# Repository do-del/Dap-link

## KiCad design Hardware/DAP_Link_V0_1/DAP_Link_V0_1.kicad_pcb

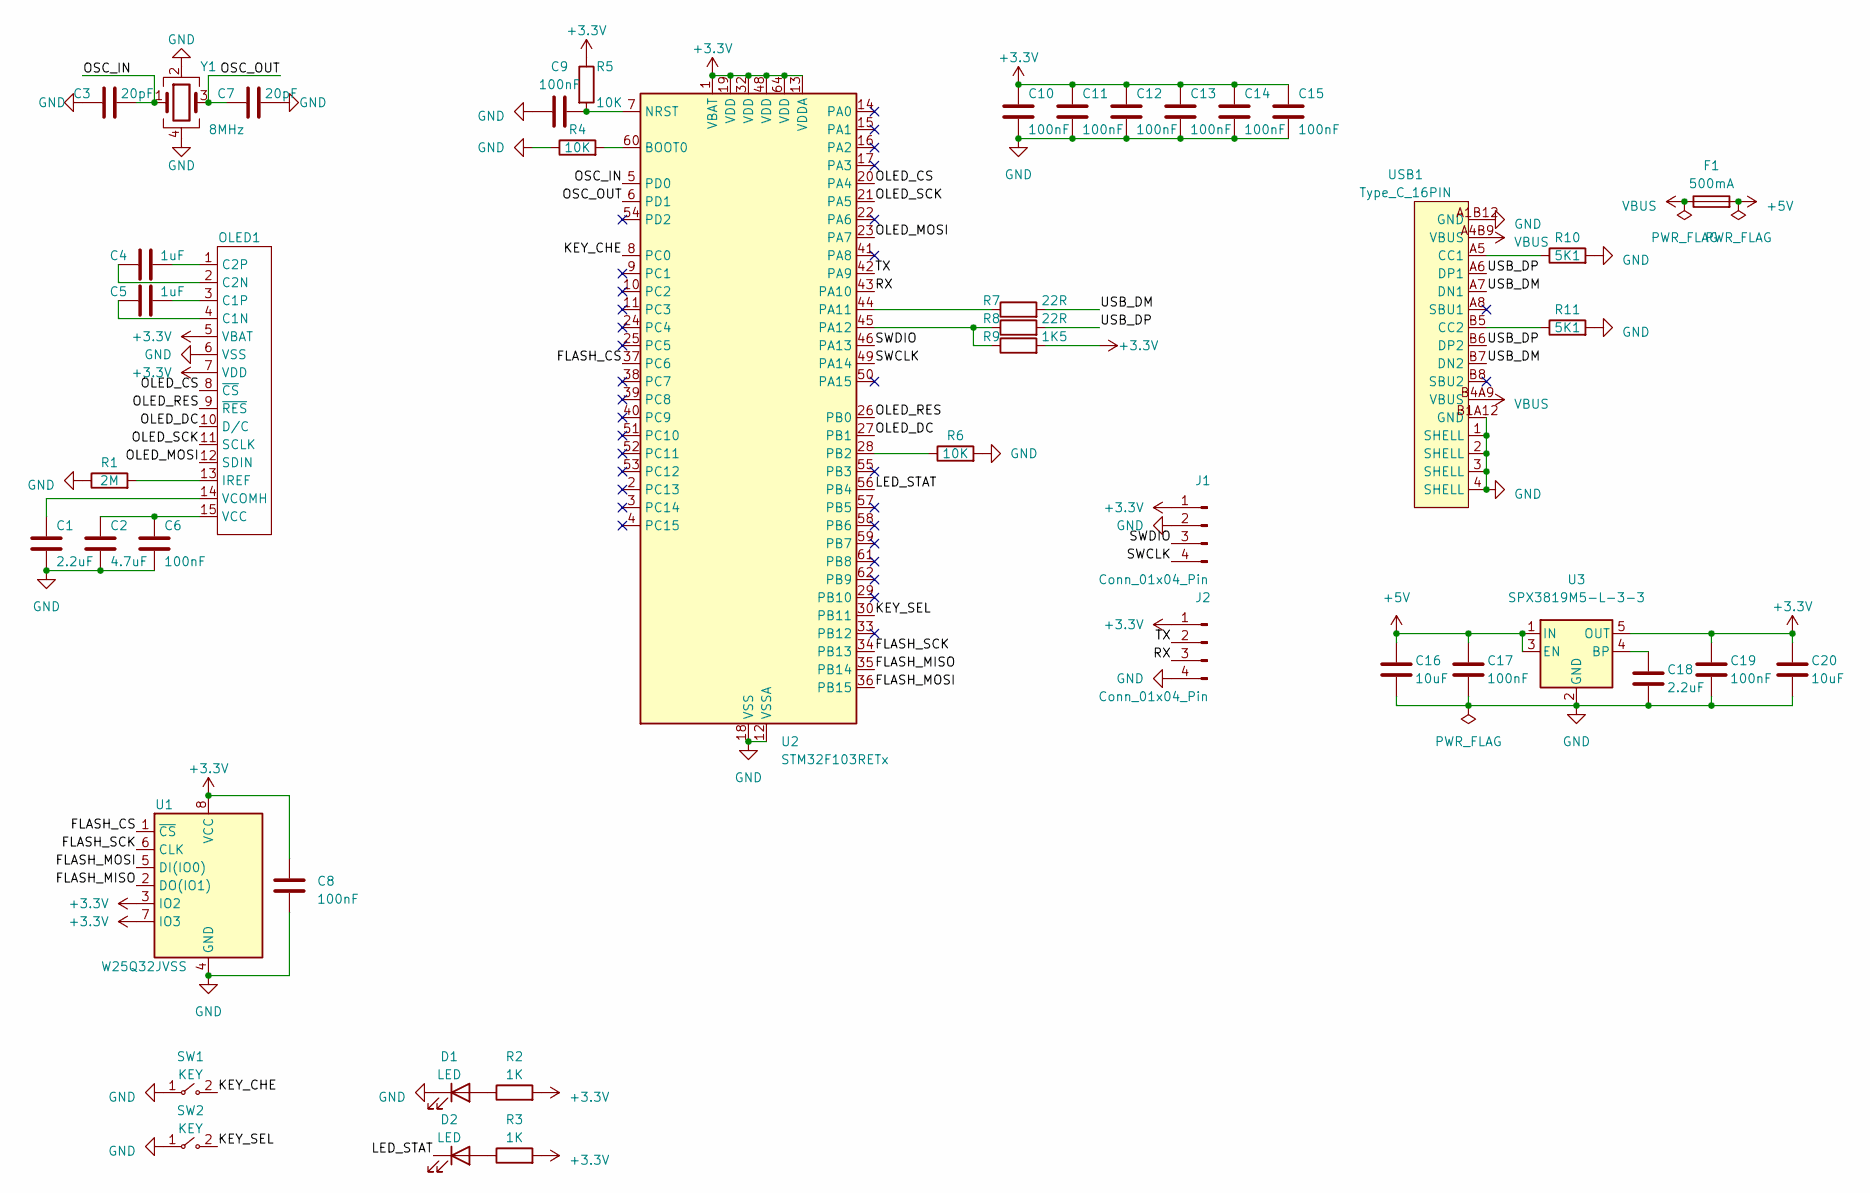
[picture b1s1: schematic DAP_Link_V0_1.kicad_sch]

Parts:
C1, C18: 2.2uF; C_0603_1608Metric_Pad1.08x0.95mm_HandSolder
C2: 4.7uF; C_0603_1608Metric_Pad1.08x0.95mm_HandSolder
C3, C7: 20pF; C_0603_1608Metric_Pad1.08x0.95mm_HandSolder
C4, C5: 1uF; C_0603_1608Metric_Pad1.08x0.95mm_HandSolder
C6, C8, C9, C10, C11, C12, C13, C14, C15, C17, C19: 100nF; C_0603_1608Metric_Pad1.08x0.95mm_HandSolder
C16, C20: 10uF; C_0603_1608Metric_Pad1.08x0.95mm_HandSolder
D1, D2: LED; LED_0603_1608Metric_Pad1.05x0.95mm_HandSolder
F1: 500mA; Fuse_1206_3216Metric
J1: Conn_01x04_Pin; SH1.0mm_4P_WT
J2: Conn_01x04_Pin; Conn_2.54_01x04_SMD_V
OLED1: 0.91_OLED_15P
R1: 2M; R_0603_1608Metric_Pad0.98x0.95mm_HandSolder
R2, R3: 1K; R_0603_1608Metric_Pad0.98x0.95mm_HandSolder
R4, R5, R6: 10K; R_0603_1608Metric_Pad0.98x0.95mm_HandSolder
R7, R8: 22R; R_0603_1608Metric_Pad0.98x0.95mm_HandSolder
R9: 1K5; R_0603_1608Metric_Pad0.98x0.95mm_HandSolder
R10, R11: 5K1; R_0603_1608Metric_Pad0.98x0.95mm_HandSolder
SW1, SW2: KEY; SW_3x4
U1: W25Q32JVSS; SOIC-8_5.23x5.23mm_P1.27mm
U2: STM32F103RETx; LQFP-64_10x10mm_P0.5mm
U3: SPX3819M5-L-3-3; SOT-23-5
USB1: Type_C_16PIN; TYPE-C-16PIN_SMD
Y1: 8MHz; Crystal_SMD_3225-4Pin_3.2x2.5mm

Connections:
+3.3V: C8.2, C10.1, C11.1, C12.1, C13.1, C14.1, C15.1, C19.1, C20.1, J1.1, J2.1, OLED1.5 (VBAT), OLED1.7 (VDD), R2.2, R3.2, R5.1, R9.2, U1.3 (IO2), U1.7 (IO3), U1.8 (VCC), U2.1 (VBAT), U2.13 (VDDA), U2.19 (VDD), U2.32 (VDD), U2.48 (VDD), U2.64 (VDD), U3.5 (OUT)
+5V: C16.1, C17.1, F1.2, U3.1 (IN), U3.3 (EN)
/FLASH_CS: U1.1 (~CS), U2.37 (PC6)
/FLASH_MISO: U1.2 (DO(IO1)), U2.35 (PB14)
/FLASH_MOSI: U1.5 (DI(IO0)), U2.36 (PB15)
/FLASH_SCK: U1.6 (CLK), U2.34 (PB13)
/KEY_CHE: SW1.2 (B), U2.8 (PC0)
/KEY_SEL: SW2.2 (B), U2.30 (PB11)
/LED_STAT: D2.1 (K), U2.56 (PB4)
/OLED_CS: OLED1.8 (~CS), U2.20 (PA4)
/OLED_DC: OLED1.10 (D/C), U2.27 (PB1)
/OLED_MOSI: OLED1.12 (SDIN), U2.23 (PA7)
/OLED_RES: OLED1.9 (~RES), U2.26 (PB0)
/OLED_SCK: OLED1.11 (SCLK), U2.21 (PA5)
/OSC_IN: C3.2, U2.5 (PD0), Y1.1
/OSC_OUT: C7.1, U2.6 (PD1), Y1.3
/RX: J2.3, U2.43 (PA10)
/SWCLK: J1.4, U2.49 (PA14)
/SWDIO: J1.3, U2.46 (PA13)
/TX: J2.2, U2.42 (PA9)
/USB_DM: R7.2, USB1.A7 (DN1), USB1.B7 (DN2)
/USB_DP: R8.2, USB1.A6 (DP1), USB1.B6 (DP2)
GND: C1.2, C2.2, C3.1, C6.2, C7.2, C8.1, C9.1, C10.2, C11.2, C12.2, C13.2, C14.2, C15.2, C16.2, C17.2, C18.2, C19.2, C20.2, D1.1 (K), J1.2, J2.4, OLED1.6 (VSS), R1.1, R4.1, R6.2, R10.2, R11.2, SW1.1 (A), SW2.1 (A), U1.4 (GND), U2.12 (VSSA), U2.18 (VSS), U2.31 (VSS), U2.47 (VSS), U2.63 (VSS), U3.2 (GND), USB1.1 (SHELL), USB1.2 (SHELL), USB1.3 (SHELL), USB1.4 (SHELL), USB1.A1B12 (GND), USB1.B1A12 (GND), Y1.2, Y1.4
unnamed: D1.2 (A), R2.1
unnamed: D2.2 (A), R3.1
unnamed: C5.1, OLED1.4 (C1N)
unnamed: C5.2, OLED1.3 (C1P)
unnamed: C4.1, OLED1.2 (C2N)
unnamed: C4.2, OLED1.1 (C2P)
unnamed: OLED1.13 (IREF), R1.2
unnamed: C2.1, C6.1, OLED1.15 (VCC)
unnamed: C1.1, OLED1.14 (VCOMH)
unnamed: R4.2, U2.60 (BOOT0)
unnamed: C9.2, R5.2, U2.7 (NRST)
unnamed: R7.1, U2.44 (PA11)
unnamed: R8.1, R9.1, U2.45 (PA12)
unnamed: R6.1, U2.28 (PB2)
unnamed: C18.1, U3.4 (BP)
unnamed: R10.1, USB1.A5 (CC1)
unnamed: R11.1, USB1.B5 (CC2)
VBUS: F1.1, USB1.A4B9 (VBUS), USB1.B4A9 (VBUS)

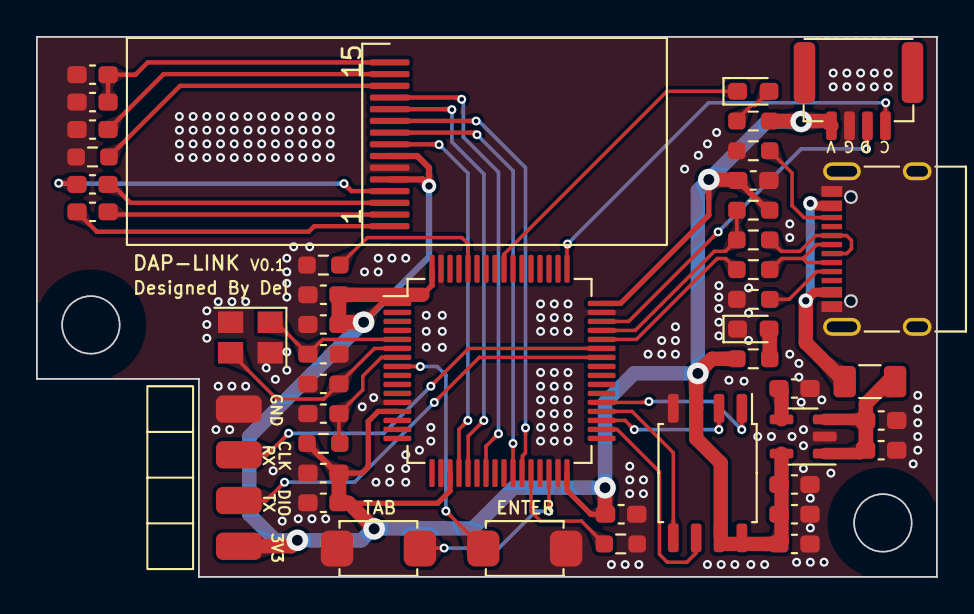
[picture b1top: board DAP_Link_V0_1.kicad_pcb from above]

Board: 2 copper layers, 50.0 x 30.0 mm, 44 parts (0 on the bottom side), 41 nets.

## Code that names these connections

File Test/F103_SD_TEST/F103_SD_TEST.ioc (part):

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Mcu.Name=STM32F103C(8-B)Tx
Mcu.Package=LQFP48
Mcu.UserName=STM32F103C8Tx
PA11.Mode=Device
PA11.Signal=USB_DM
PA12.Mode=Device
PA12.Signal=USB_DP
PA13.Mode=Serial_Wire
PA13.Signal=SYS_JTMS-SWDIO
PA14.Mode=Serial_Wire
PA14.Signal=SYS_JTCK-SWCLK
PA4.GPIOParameters=GPIO_Speed
PA4.GPIO_Speed=GPIO_SPEED_FREQ_HIGH
PA4.Signal=GPIO_Output
PA5.Mode=Full_Duplex_Master
PA5.Signal=SPI1_SCK
PA6.Mode=Full_Duplex_Master
PA6.Signal=SPI1_MISO
PA7.Mode=Full_Duplex_Master
PA7.Signal=SPI1_MOSI
PC14-OSC32_IN.Mode=LSE-External-Oscillator
PC14-OSC32_IN.Signal=RCC_OSC32_IN
PC15-OSC32_OUT.Mode=LSE-External-Oscillator
PC15-OSC32_OUT.Signal=RCC_OSC32_OUT
PD0-OSC_IN.Mode=HSE-External-Oscillator
PD0-OSC_IN.Signal=RCC_OSC_IN
PD1-OSC_OUT.Mode=HSE-External-Oscillator
PD1-OSC_OUT.Signal=RCC_OSC_OUT
RCC.SYSCLKFreq_VALUE=48000000
RCC.SYSCLKSource=RCC_SYSCLKSOURCE_PLLCLK
board=custom

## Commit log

2023-03-03 创建项目
2023-03-08 PCB v0.1验证通过
2023-03-09 添加SD卡USB读写程序
